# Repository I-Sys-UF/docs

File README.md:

# docs

部内 Wiki 的なやつ

作成時は branch を切ってください．ファイルの作成方法は既存のものを真似るようにお願いします

- [GitHub について](./GitHub/GitHub.md)
- [KiCAD の使い方](./KiCAD/KiCAD.md)
- [なぜプログラミングをするのか](./zatsu/why_programming.md)
- [プログラミングの始め方 with Trainer](./edu/getting_started_programming)
- [Trainer でプログラミングを学ぼう](./edu/train-with-traner/)
- [78xx の使い方](./circuit/78xx)
- [資料の書き方・作り方](./GitHub/how_to_create_docs.md)

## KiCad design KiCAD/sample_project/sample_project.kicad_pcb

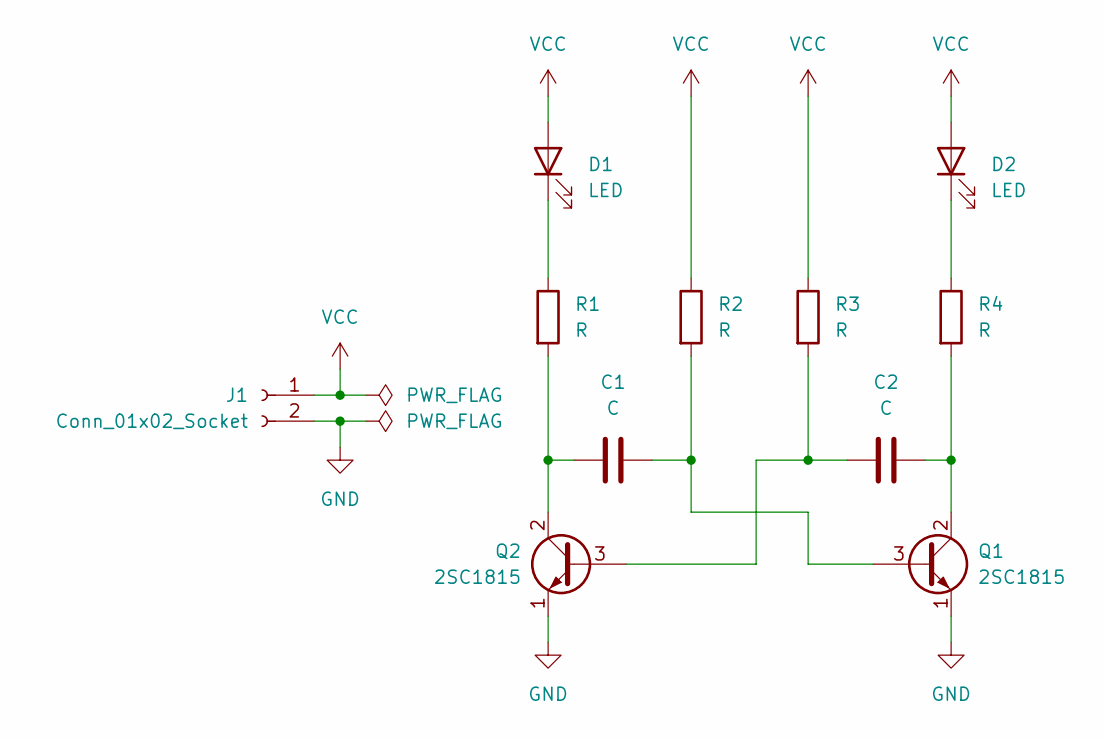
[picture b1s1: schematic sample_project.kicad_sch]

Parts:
C1, C2: C; CP_Radial_D5.0mm_P2.00mm
D1, D2: LED; LED_D5.0mm
J1: Conn_01x02_Socket; PinSocket_1x02_P2.54mm_Vertical
Q1, Q2: 2SC1815; TO-92_Inline
R1, R2, R3, R4: R; R_Axial_DIN0204_L3.6mm_D1.6mm_P7.62mm_Horizontal

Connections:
GND: J1.2, Q1.1 (E), Q2.1 (E)
unnamed: D1.1 (K), R1.1
unnamed: D2.1 (K), R4.1
unnamed: C1.2, Q1.3 (B), R2.2
unnamed: C2.1, Q1.2 (C), R4.2
unnamed: C2.2, Q2.3 (B), R3.2
unnamed: C1.1, Q2.2 (C), R1.2
VCC: D1.2 (A), D2.2 (A), J1.1, R2.1, R3.1

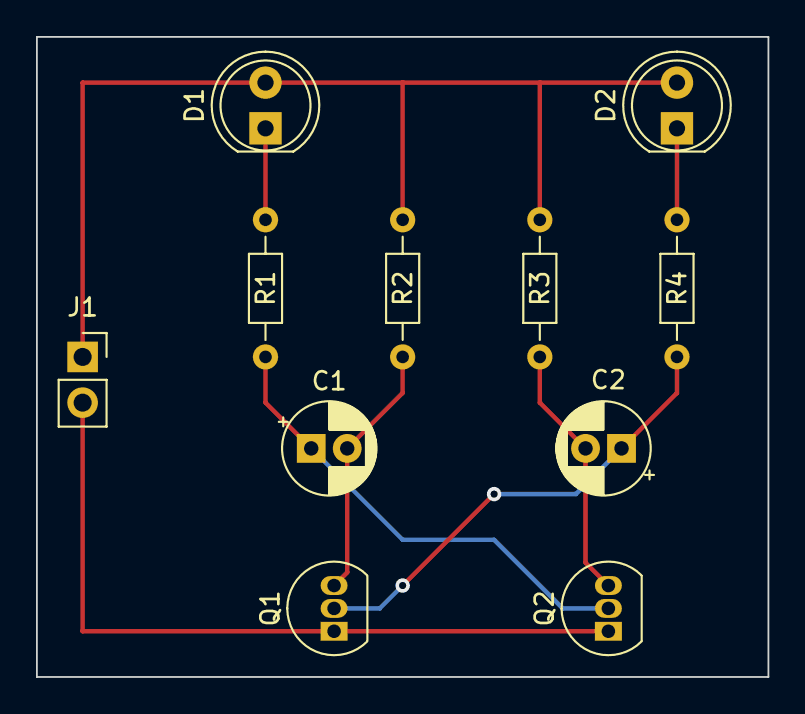
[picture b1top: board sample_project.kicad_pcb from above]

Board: 2 copper layers, 40.6 x 35.6 mm, 11 parts (0 on the bottom side), 8 nets.

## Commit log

2023-07-24 リンク追加
2023-08-08 Create file
2023-08-08 資料作成
2023-08-08 PDF ファイルをアップロード
2023-08-09 パスを変更
2023-08-09 ドキュメント追加
2023-08-09 画像追加
2023-08-09 注意点追加
2023-08-09 ファイル階層変更
2023-08-09 タイトル変更
2023-08-09 配置変更
2023-08-09 基板データ追加
2023-10-06 文言を微修正
2023-11-24 GitHub の使い方に関する項目を追加
2023-11-24 若干表現を修正
2023-11-24 GitHub 追加
2023-11-24 rename
2023-11-25 GitHub Markdown のリンクを追加
2024-05-09 Rename getting_started_programming.md to getting_started_programming.md
2024-05-10 replace and
2024-05-10 fix link
2024-05-10 change image size
2024-05-10 update title
2024-05-10 fix title
2024-05-10 ちょっと修正
2024-05-10 書き込み方法追記
2024-06-14 第三節作成
2024-06-15 第四節追加
2024-06-18 第五節追加
2024-06-25 第六節途中経過保存
2024-10-04 誤字 fix
2024-11-07 一旦 commit
2024-11-16 markdown の資料作成
